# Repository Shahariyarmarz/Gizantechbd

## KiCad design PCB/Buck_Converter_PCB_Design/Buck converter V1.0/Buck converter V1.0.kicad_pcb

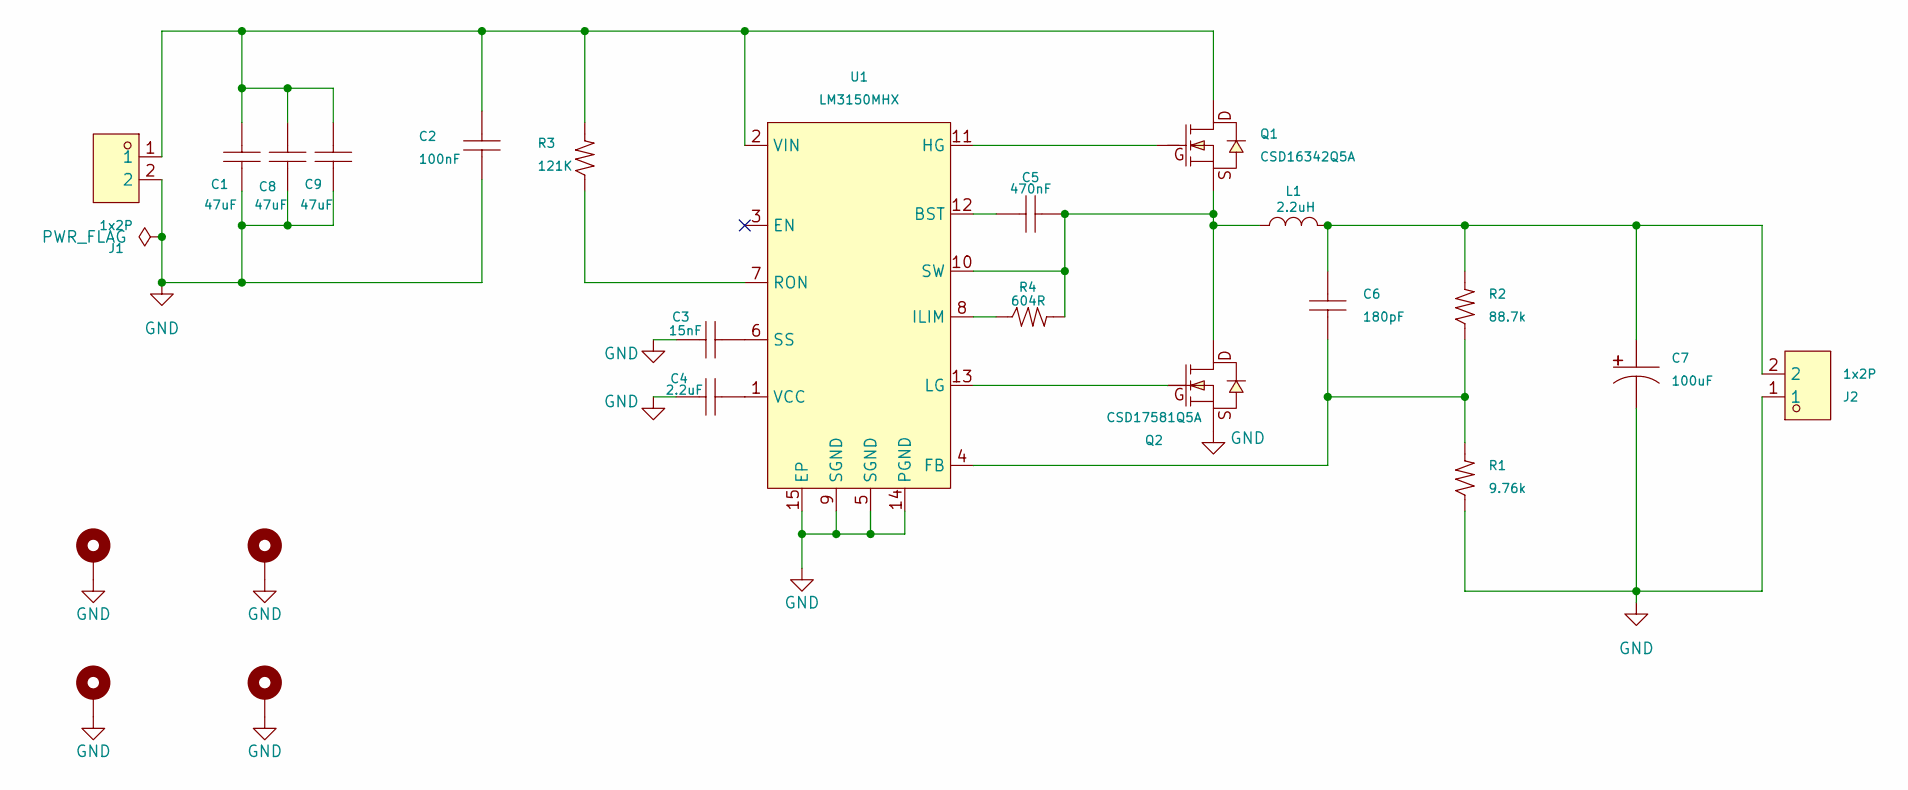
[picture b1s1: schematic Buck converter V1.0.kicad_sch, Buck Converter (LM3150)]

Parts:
C1, C8, C9: 47uF; C1206; MPN GRM31CR61E476ME44L; LCSC Part ID C403725
C2: 100nF; C1206; MPN TCC1206M3L104J250FT; LCSC Part ID C20539429
C3: 15nF; C0603; MPN CC0603JRX7R8BB153; LCSC Part ID C519541
C4: 2.2uF; C0805; MPN GRM21BR71A225KA01L; LCSC Part ID C117966
C5: 470nF; C1206; MPN ECPU1C474MA5; LCSC Part ID C178432
C6: 180pF; C0805; MPN CC0805JRNPO9BN181; LCSC Part ID C113826
C7: 100uF; SMD,D6.3xL5.8mm; MPN 16SVPC100M; LCSC Part ID C136275
H1, H2, H3, H4: MountingHole_Pad; MountingHole_3.2mm_M3_Pad_Via
J1, J2: 1x2P; ST-2P-Plugin,P=5.08mm; MPN JL500-50802G01_C709041; LCSC Part ID C709041
L1: 2.2uH; IND-SMD_L13.2-W12.9_MMD-12FD; MPN IHLP5050CEER2R2M01; LCSC Part ID C845090
Q1: CSD16342Q5A; PQFN-8_L5.8-W4.9-P1.27-LS6.0-BL; MPN CSD16342Q5A; LCSC Part ID C2760459
Q2: CSD17581Q5A; DFN-8_L5.8-W4.9-P1.27-LS6.0-BL-1; MPN CSD17581Q5A; LCSC Part ID C471056
R1: 9.76k; R0603; MPN RC0603FR-079K76L; LCSC Part ID C137665
R2: 88.7k; R1206; MPN RC1206FR-0788K7L; LCSC Part ID C488995
R3: 121K; R0805; MPN RC0805FR-07121KL; LCSC Part ID C273848
R4: 604R; R1206; MPN RC1206FR-07604RL; LCSC Part ID C274099
U1: LM3150MHX; HTSSOP-14_L5.0-W4.4-P0.65-LS6.4-BL-EP; MPN LM3150MHX; LCSC Part ID C48112

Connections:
GND: C1.1, C2.1, C3.1, C4.2, C7.2, C8.1, C9.1, H1.1, H2.1, H3.1, H4.1, J1.2, J2.1, Q2.1 (S), Q2.2 (S), Q2.3 (S), R1.1, U1.5 (SGND), U1.9 (SGND), U1.14 (PGND), U1.15 (EP)
unnamed: C6.2, C7.1, J2.2, L1.2, R2.2
unnamed: Q1.4 (G), U1.11 (HG)
unnamed: Q2.4 (G), U1.13 (LG)
unnamed: C5.1, U1.12 (BST)
unnamed: C6.1, R1.2, R2.1, U1.4 (FB)
unnamed: R4.1, U1.8 (ILIM)
unnamed: R3.1, U1.7 (RON)
unnamed: C3.2, U1.6 (SS)
unnamed: C5.2, L1.1, Q1.1 (S), Q1.2 (S), Q1.3 (S), Q2.5 (D), Q2.6 (D), Q2.7 (D), Q2.8 (D), Q2.9 (D), R4.2, U1.10 (SW)
unnamed: C4.1, U1.1 (VCC)
unnamed: C1.2, C2.2, C8.2, C9.2, J1.1, Q1.5 (D), Q1.6 (D), Q1.7 (D), Q1.8 (D), Q1.9 (D), R3.2, U1.2 (VIN)

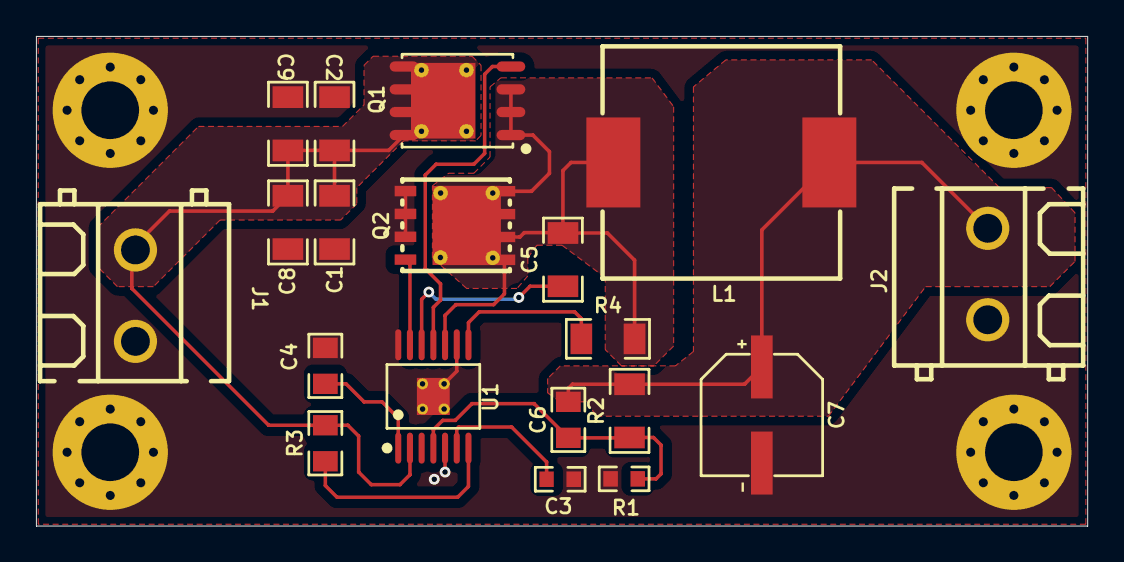
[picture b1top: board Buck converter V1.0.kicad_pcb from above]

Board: 2 copper layers, 58.4 x 27.2 mm, 23 parts (0 on the bottom side), 12 nets.

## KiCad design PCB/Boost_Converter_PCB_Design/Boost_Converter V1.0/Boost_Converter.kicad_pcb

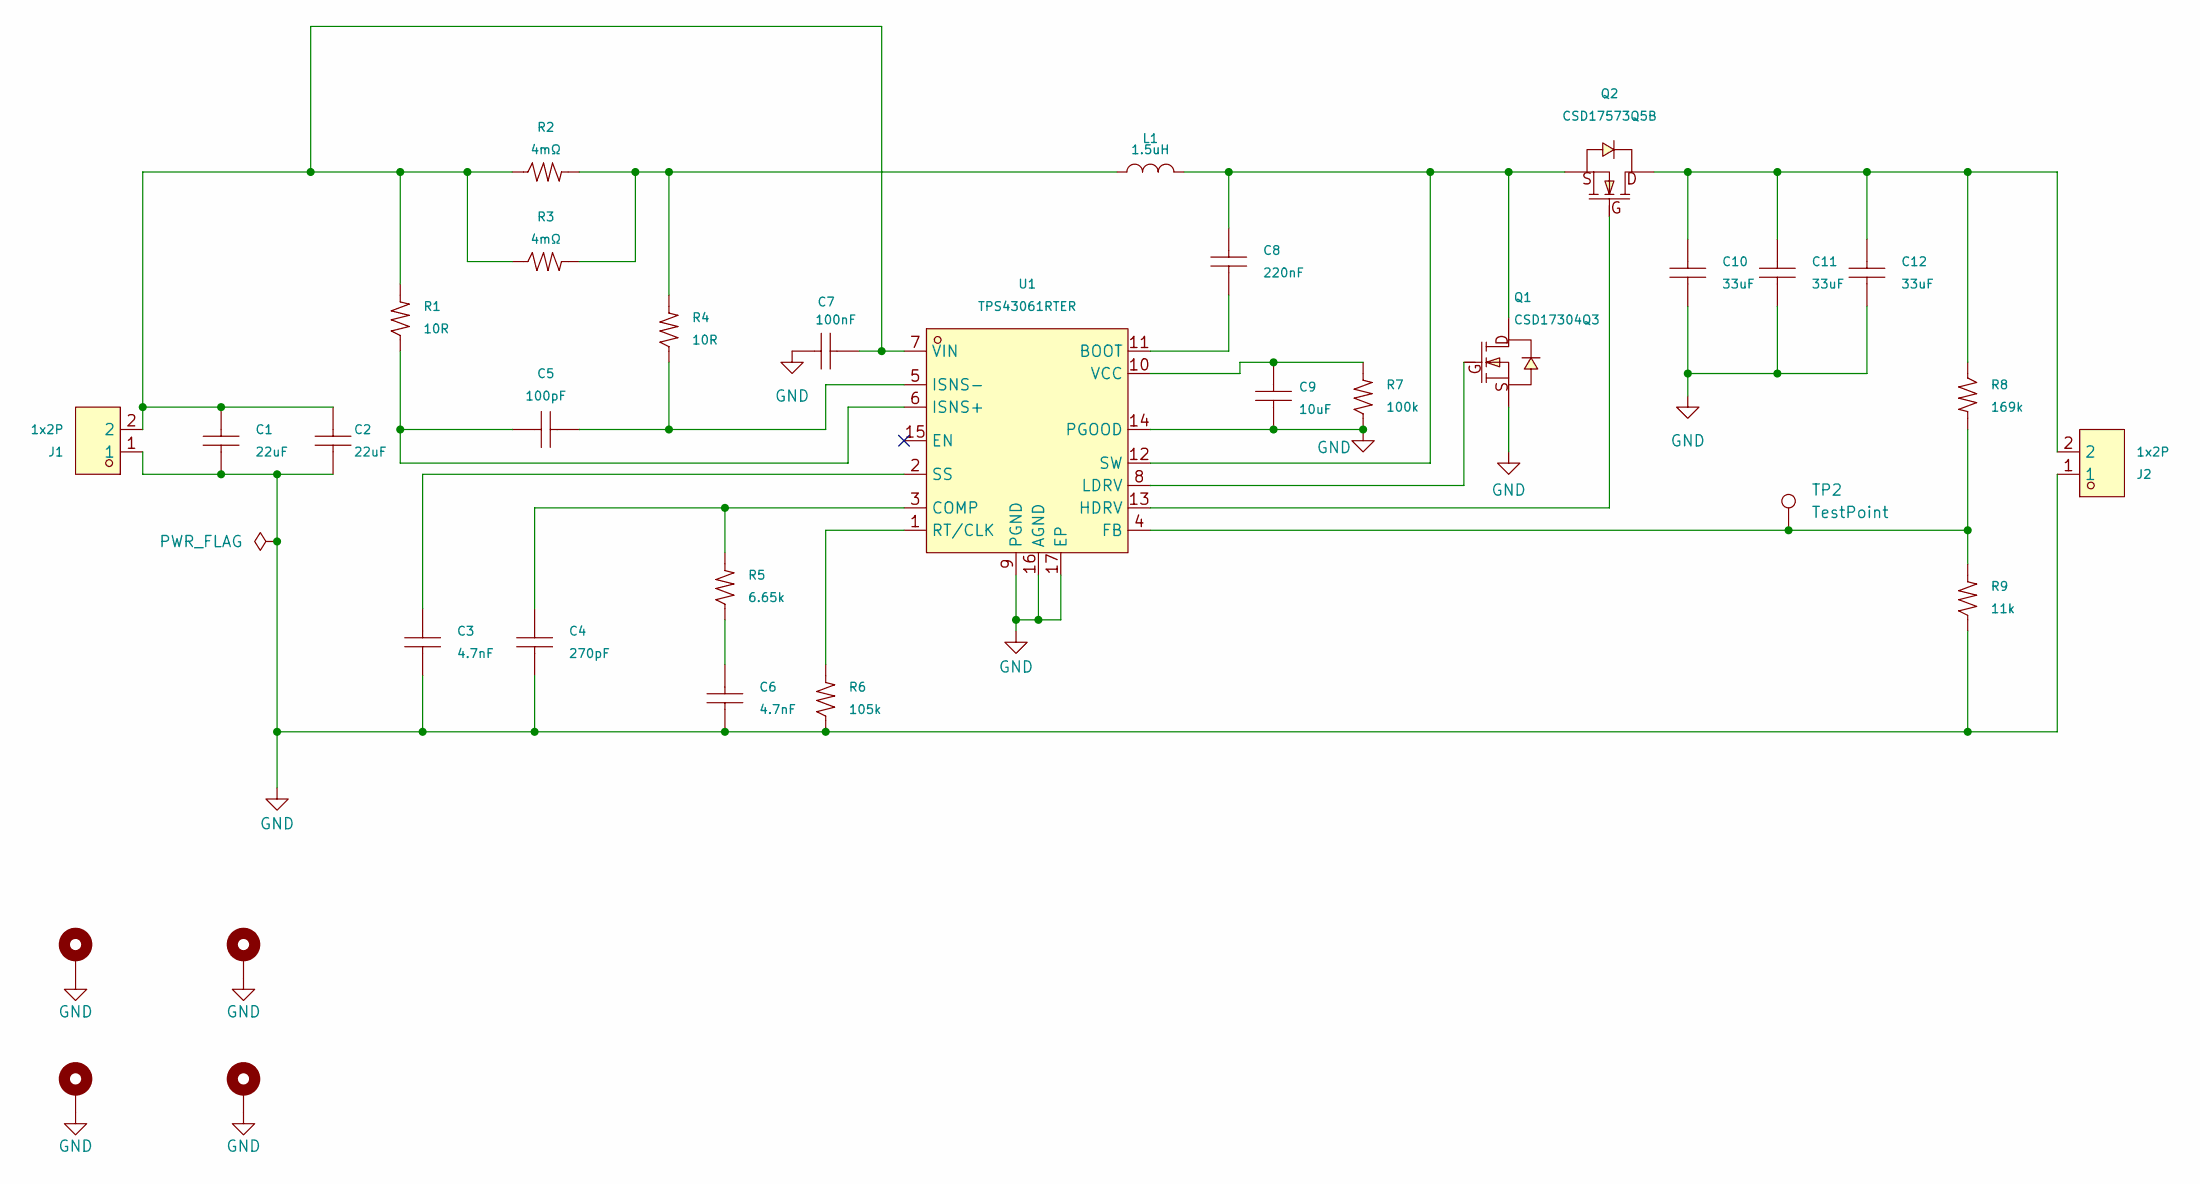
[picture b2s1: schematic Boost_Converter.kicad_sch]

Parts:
C1, C2: 22uF; C0603; MPN CL10A226MQ8NRNC; LCSC Part ID C59461
C3, C6: 4.7nF; C0603; MPN AC0603KRX7R9BB472; LCSC Part ID C149615
C4: 270pF; C0603; MPN CC0603JRNPO9BN271; LCSC Part ID C107046
C5: 100pF; C0603; MPN CC0603JRNPO9BN101; LCSC Part ID C14665
C7: 100nF; C0603; MPN CC0603KRX7R9BB104; LCSC Part ID C14663
C8: 220nF; C0603; MPN CL10B224KA8NNNC; LCSC Part ID C21120
C9: 10uF; C0603; MPN GRM188R61E106KA73D; LCSC Part ID C344022
C10, C11, C12: 33uF; C1206; MPN C3216X5R1E336MT000E; LCSC Part ID C342307
H1, H2, H3, H4: MountingHole_Pad; MountingHole_3.2mm_M3_Pad_Via
J1, J2: 1x2P; ST-2P-Plugin,P=5.08mm; MPN DB127V-5.08-2P-GN-S; LCSC Part ID C3018698
L1: 1.5uH; IND-SMD_L17.5-W17.5; MPN CKST1707-1.5UH/M; LCSC Part ID C3002739
Q1: CSD17304Q3; VSON-CLIP-8_L3.3-W3.3-P0.65-BL; MPN CSD17304Q3; LCSC Part ID C129941
Q2: CSD17573Q5B; POWERVDFN-8_L6.0-W5.0-P1.27-BL; MPN CSD17573Q5B; LCSC Part ID C202231
R1, R4: 10R; R0603; MPN RC0603FR-0710RL; LCSC Part ID C109318
R2, R3: 4mΩ; R2512; MPN HOJLR2512-3W-4MR-1%; LCSC Part ID C2904236
R5: 6.65k; R0603; MPN SCR0603F6K65; LCSC Part ID C3016441
R6: 105k; R0603; MPN FRC0603F1053TS; LCSC Part ID C2933128
R7: 100k; R0603; MPN RC0603FR-07100KL; LCSC Part ID C14675
R8: 169k; R0603; MPN RC0603FR-07169KL; LCSC Part ID C137791
R9: 11k; R0603; MPN RC0603FR-0711KL; LCSC Part ID C137801
TP2: TestPoint; TestPoint_Keystone_5000-5004_Miniature
U1: TPS43061RTER; WQFN-16_L3.0-W3.0-P0.50-BL-EP; MPN TPS43061RTER; LCSC Part ID C527683

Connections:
GND: C1.1, C2.1, C3.1, C4.1, C6.1, C7.2, C9.1, C10.1, C11.1, C12.1, H1.1, H2.1, H3.1, H4.1, J1.1, J2.1, Q1.1 (S), Q1.2 (S), Q1.3 (S), R6.1, R7.1, R9.1, U1.9 (PGND), U1.14 (PGOOD), U1.16 (AGND), U1.17 (EP)
unnamed: C6.2, R5.1
unnamed: C10.2, C11.2, C12.2, J2.2, Q2.5 (D), Q2.6 (D), Q2.7 (D), Q2.8 (D), Q2.9 (D), R8.1
unnamed: L1.1, R2.2, R3.2, R4.2
unnamed: Q1.4 (G), U1.8 (LDRV)
unnamed: Q2.4 (G), U1.13 (HDRV)
unnamed: C8.1, U1.11 (BOOT)
unnamed: C4.2, R5.2, U1.3 (COMP)
unnamed: R8.2, R9.2, TP2.1, U1.4 (FB)
unnamed: C5.2, R1.1, U1.6 (ISNS+)
unnamed: C5.1, R4.1, U1.5 (ISNS-)
unnamed: R6.2, U1.1 (RT/CLK)
unnamed: C3.2, U1.2 (SS)
unnamed: C8.2, L1.2, Q1.5 (D), Q1.6 (D), Q1.7 (D), Q1.8 (D), Q2.1 (S), Q2.2 (S), Q2.3 (S), U1.12 (SW)
unnamed: C9.2, R7.2, U1.10 (VCC)
unnamed: C1.2, C2.2, C7.1, J1.2, R1.2, R2.1, R3.1, U1.7 (VIN)

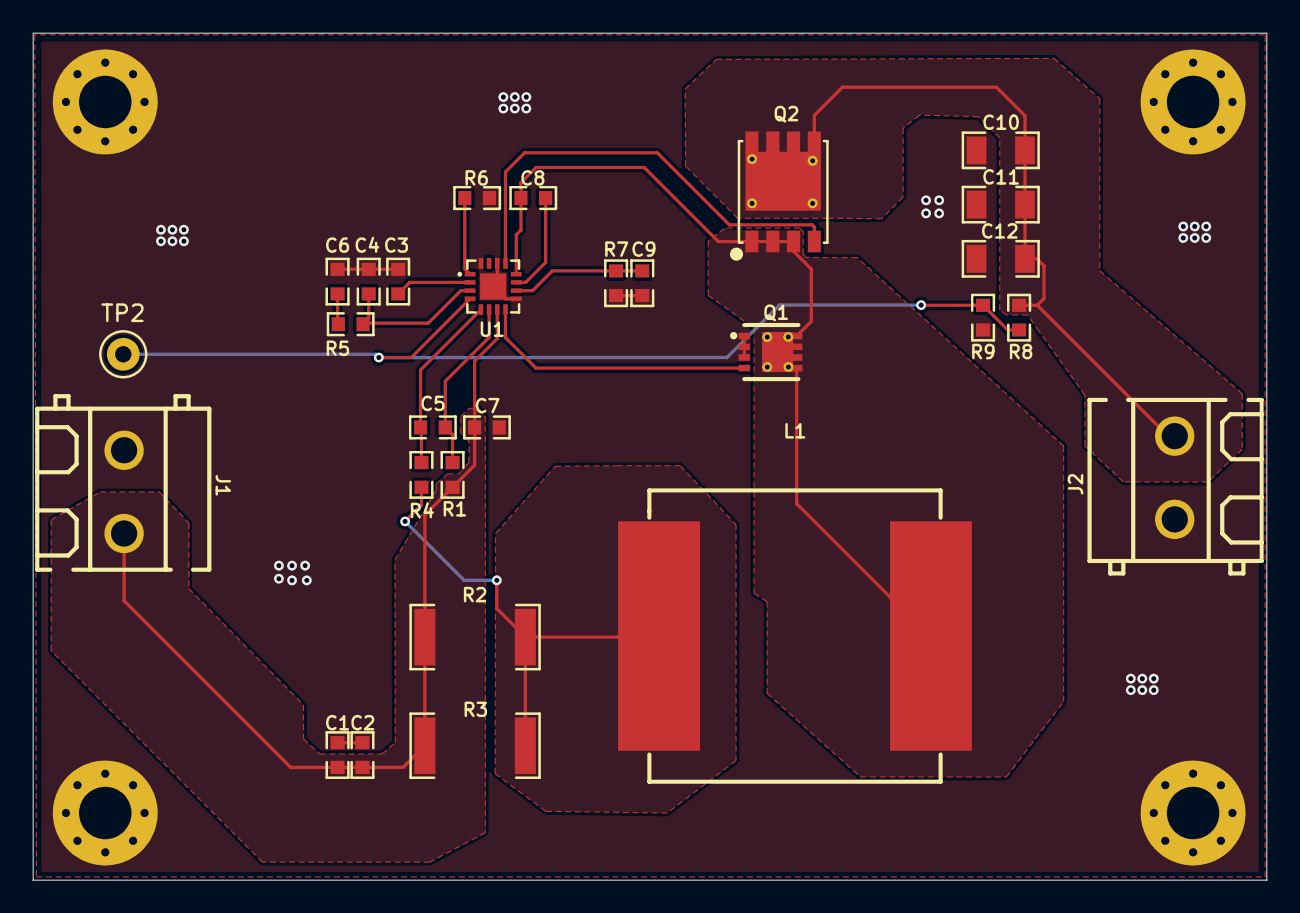
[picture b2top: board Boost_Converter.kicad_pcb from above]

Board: 2 copper layers, 75.3 x 51.7 mm, 32 parts (0 on the bottom side), 16 nets.
